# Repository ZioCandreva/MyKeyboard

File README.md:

# MyKeyboard
 My first DIY keyboard PCB

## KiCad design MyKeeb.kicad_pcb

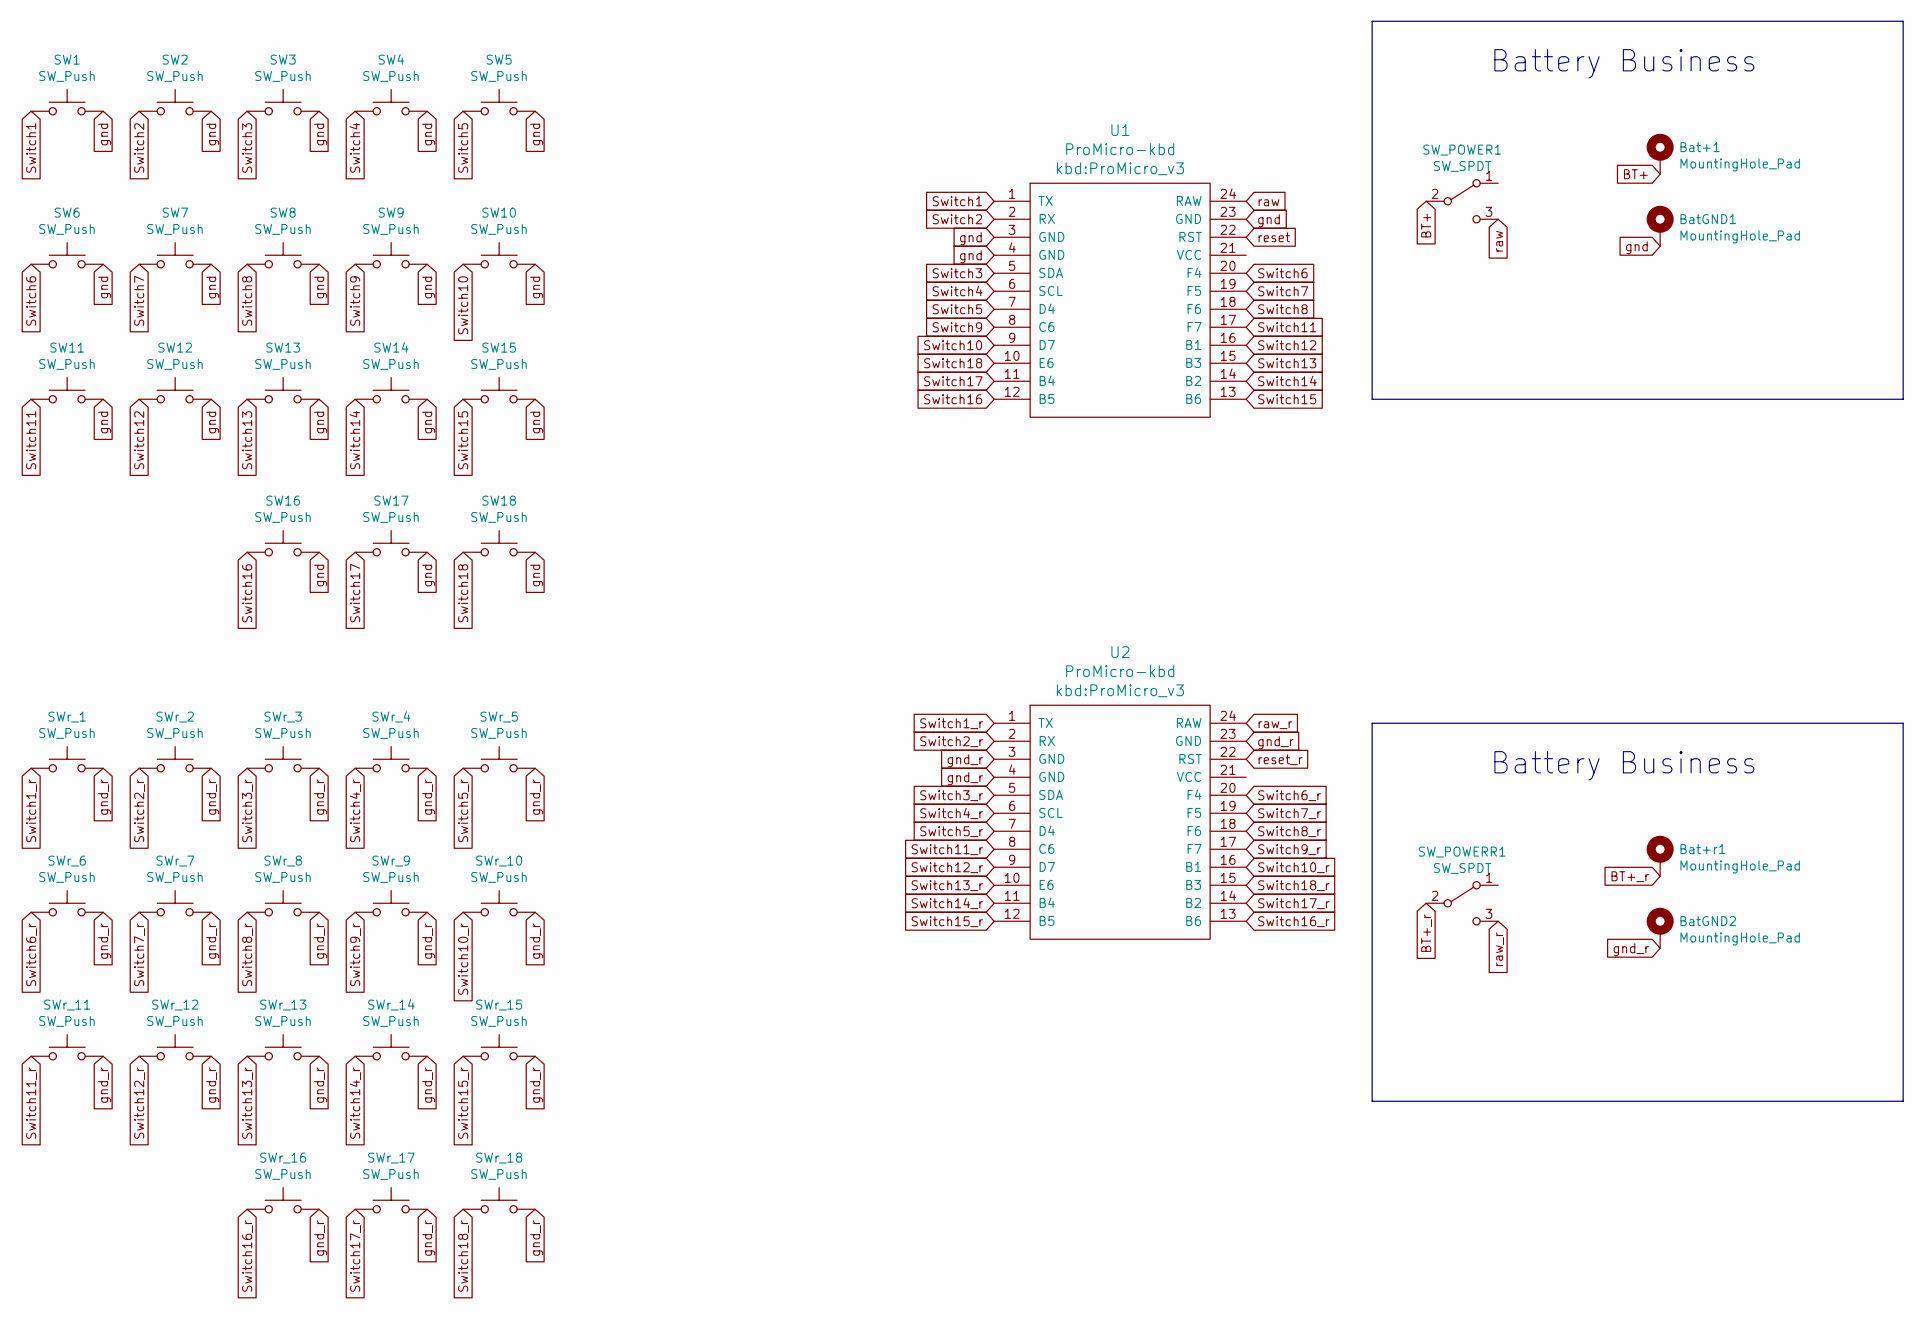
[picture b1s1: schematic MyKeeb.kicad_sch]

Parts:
Bat+1: MountingHole_Pad; 1pin_conn
Bat+r1: MountingHole_Pad; 1pin_conn
BatGND1, BatGND2: MountingHole_Pad; 1pin_conn
SW1, SW2, SW3, SW4, SW5, SW6, SW7, SW8, SW9, SW10, SW11, SW12, SW13, SW14, SW15, SW16, SW17, SW18: SW_Push; Khail_SW_sweep
SW_POWER1: SW_SPDT
SW_POWERR1: SW_SPDT
SWr_1, SWr_2, SWr_3, SWr_4, SWr_5, SWr_6, SWr_7, SWr_8, SWr_9, SWr_10, SWr_11, SWr_12, SWr_13, SWr_14, SWr_15, SWr_16, SWr_17, SWr_18: SW_Push; Khail_SW_sweep
U1, U2: ProMicro-kbd; ProMicro_v3

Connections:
BT+: Bat+1.1, SW_POWER1.2 (B)
BT+_r: Bat+r1.1, SW_POWERR1.2 (B)
Switch1: SW1.1, U1.1 (TX)
Switch1_r: SWr_1.1, U2.1 (TX)
Switch2: SW2.1, U1.2 (RX)
Switch2_r: SWr_2.1, U2.2 (RX)
Switch3: SW3.1, U1.5 (SDA)
Switch3_r: SWr_3.1, U2.5 (SDA)
Switch4: SW4.1, U1.6 (SCL)
Switch4_r: SWr_4.1, U2.6 (SCL)
Switch5: SW5.1, U1.7 (D4)
Switch5_r: SWr_5.1, U2.7 (D4)
Switch6: SW6.1, U1.20 (F4)
Switch6_r: SWr_6.1, U2.20 (F4)
Switch7: SW7.1, U1.19 (F5)
Switch7_r: SWr_7.1, U2.19 (F5)
Switch8: SW8.1, U1.18 (F6)
Switch8_r: SWr_8.1, U2.18 (F6)
Switch9: SW9.1, U1.8 (C6)
Switch9_r: SWr_9.1, U2.17 (F7)
Switch10: SW10.1, U1.9 (D7)
Switch10_r: SWr_10.1, U2.16 (B1)
Switch11: SW11.1, U1.17 (F7)
Switch11_r: SWr_11.1, U2.8 (C6)
Switch12: SW12.1, U1.16 (B1)
Switch12_r: SWr_12.1, U2.9 (D7)
Switch13: SW13.1, U1.15 (B3)
Switch13_r: SWr_13.1, U2.10 (E6)
Switch14: SW14.1, U1.14 (B2)
Switch14_r: SWr_14.1, U2.11 (B4)
Switch15: SW15.1, U1.13 (B6)
Switch15_r: SWr_15.1, U2.12 (B5)
Switch16: SW16.1, U1.12 (B5)
Switch16_r: SWr_16.1, U2.13 (B6)
Switch17: SW17.1, U1.11 (B4)
Switch17_r: SWr_17.1, U2.14 (B2)
Switch18: SW18.1, U1.10 (E6)
Switch18_r: SWr_18.1, U2.15 (B3)
gnd: BatGND1.1, SW1.2, SW2.2, SW3.2, SW4.2, SW5.2, SW6.2, SW7.2, SW8.2, SW9.2, SW10.2, SW11.2, SW12.2, SW13.2, SW14.2, SW15.2, SW16.2, SW17.2, SW18.2, U1.3 (GND), U1.4 (GND), U1.23 (GND)
gnd_r: BatGND2.1, SWr_1.2, SWr_2.2, SWr_3.2, SWr_4.2, SWr_5.2, SWr_6.2, SWr_7.2, SWr_8.2, SWr_9.2, SWr_10.2, SWr_11.2, SWr_12.2, SWr_13.2, SWr_14.2, SWr_15.2, SWr_16.2, SWr_17.2, SWr_18.2, U2.3 (GND), U2.4 (GND), U2.23 (GND)
raw: SW_POWER1.3 (C), U1.24 (RAW)
raw_r: SW_POWERR1.3 (C), U2.24 (RAW)
reset: U1.22 (RST)
reset_r: U2.22 (RST)

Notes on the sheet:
Battery Business

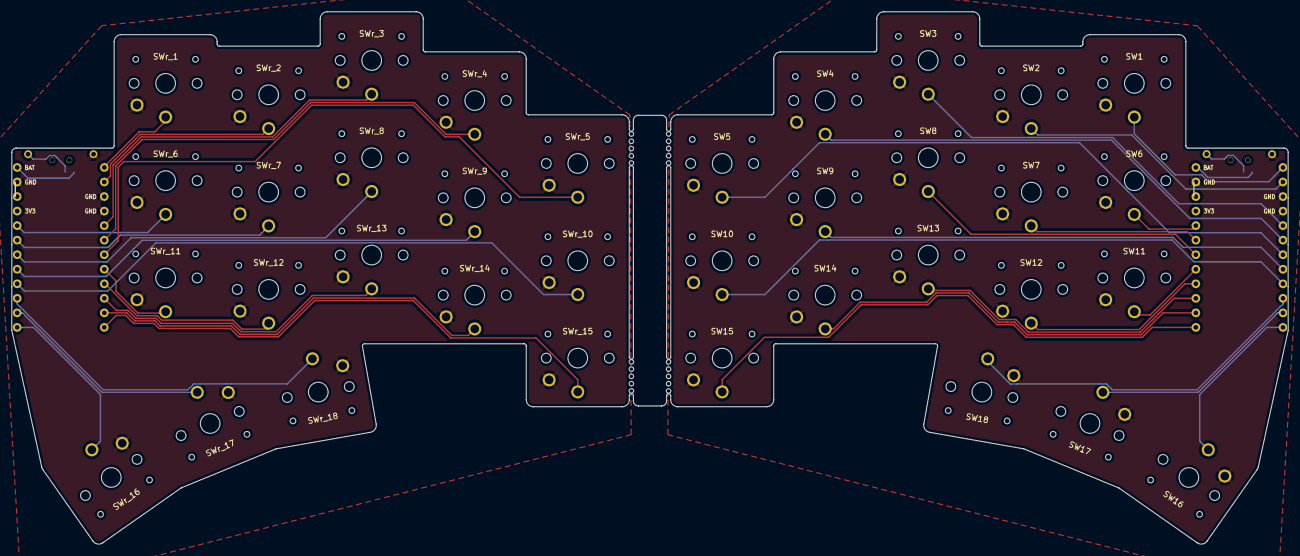
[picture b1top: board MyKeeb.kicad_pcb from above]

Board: 2 copper layers, 223.0 x 93.0 mm, 48 parts (0 on the bottom side), 42 nets.

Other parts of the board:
H1, H2, H9, H10: Mousebites; breakaway-mousebites

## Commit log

2022-09-29 wrong folder
    lel
